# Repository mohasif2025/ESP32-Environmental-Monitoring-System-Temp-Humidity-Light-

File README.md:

# ESP32-Environmental-Monitoring-System-Temp-Humidity-Light-

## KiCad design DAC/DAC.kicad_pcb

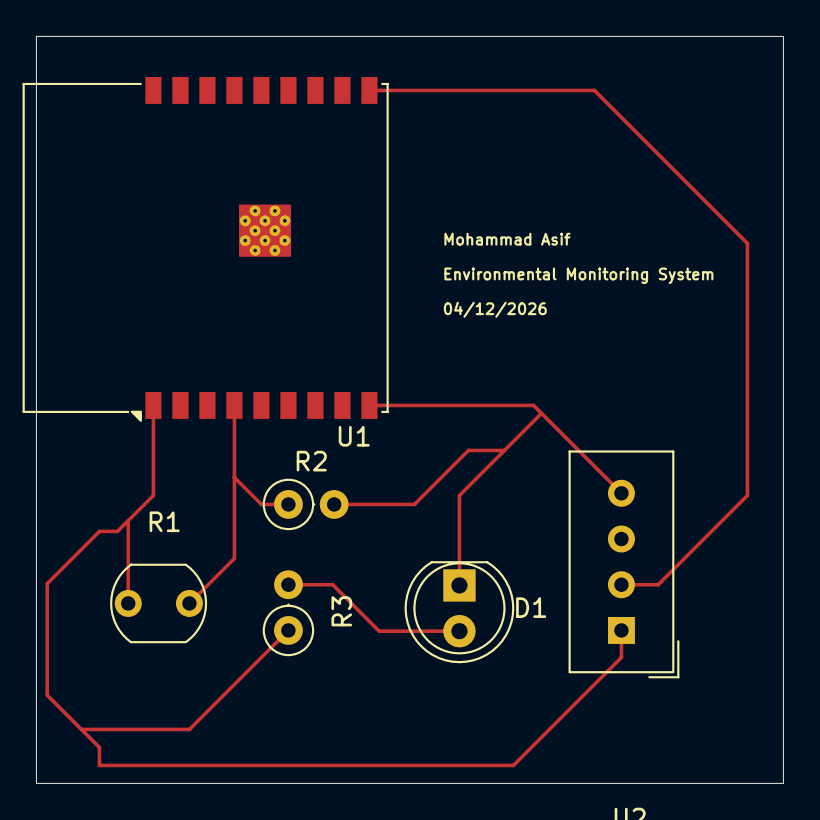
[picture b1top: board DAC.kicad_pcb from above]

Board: 2 copper layers, 41.5 x 41.5 mm, 6 parts (0 on the bottom side), 5 nets.

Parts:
D1: LED; LED_D5.0mm
R1: R_Photo; R_LDR_5.1x4.3mm_P3.4mm_Vertical
R2, R3: 10k; R_Axial_DIN0207_L6.3mm_D2.5mm_P2.54mm_Vertical
U1: ESP32-C3-WROOM-02
U2: DHT11; Aosong_DHT11_5.5x12.0_P2.54mm

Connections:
unnamed: D1.2 (A), R3.2
unnamed: D1.1 (K), R2.2, U1.9 (GND), U1.19 (GND), U2.4 (GND)
unnamed: R1.1, R3.1, U1.1 (3V3), U2.1 (VDD)
unnamed: R1.2, R2.1, U1.4 (IO5)
unnamed: U1.10 (IO10), U2.2 (DATA)

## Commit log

2026-05-22 Create Screenshots
2026-05-22 Rename DAC.kicad_pcb to DAC/DAC.kicad_pcb
2026-05-22 Rename DAC.kicad_pro to DAC/DAC.kicad_pro
2026-05-22 Rename DAC.kicad_sch to DAC/DAC.kicad_sch
2026-05-22 Rename Screenshot 2026-05-22 185413.png to pcb.png
2026-05-22 Rename Screenshot 2026-05-22 185916.png to 3Dpcb.png
2026-05-22 Rename Screenshot 2026-05-22 185938.png to schematic.png
